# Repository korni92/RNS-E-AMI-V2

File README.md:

# RNS-E-AMI-V2
Replacement for AMI with more modern features

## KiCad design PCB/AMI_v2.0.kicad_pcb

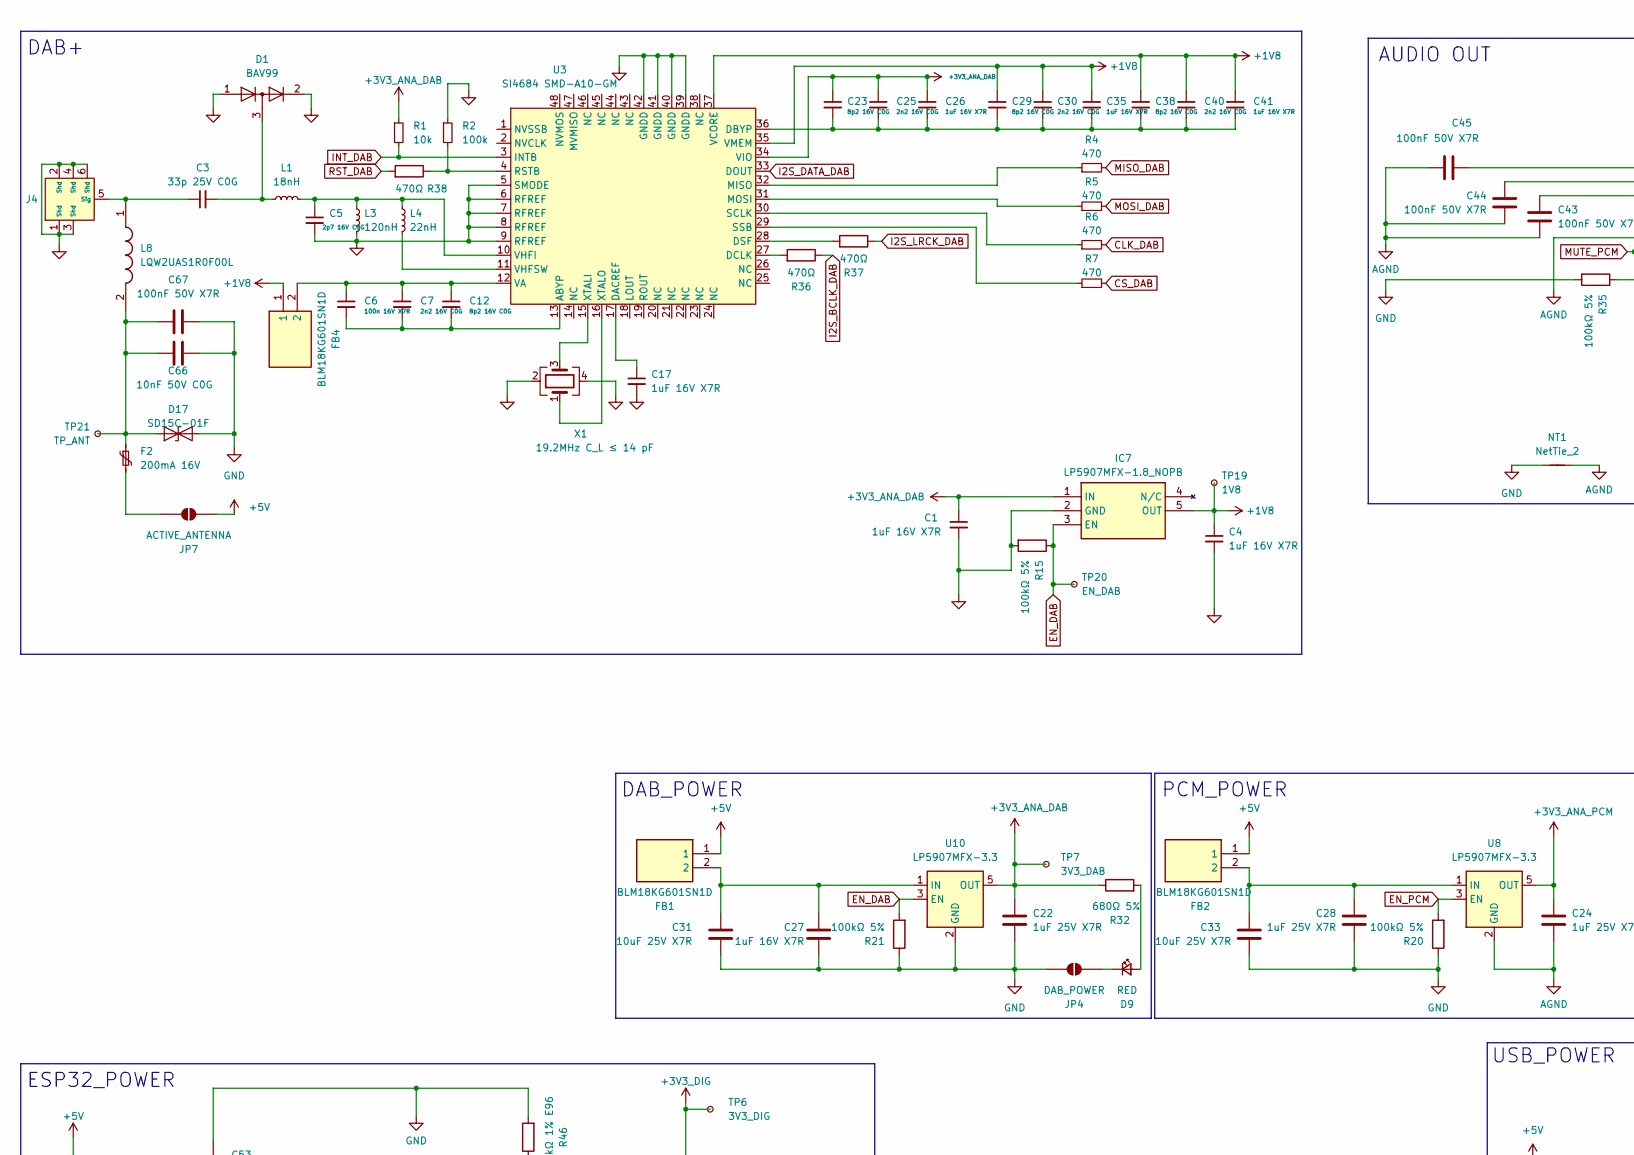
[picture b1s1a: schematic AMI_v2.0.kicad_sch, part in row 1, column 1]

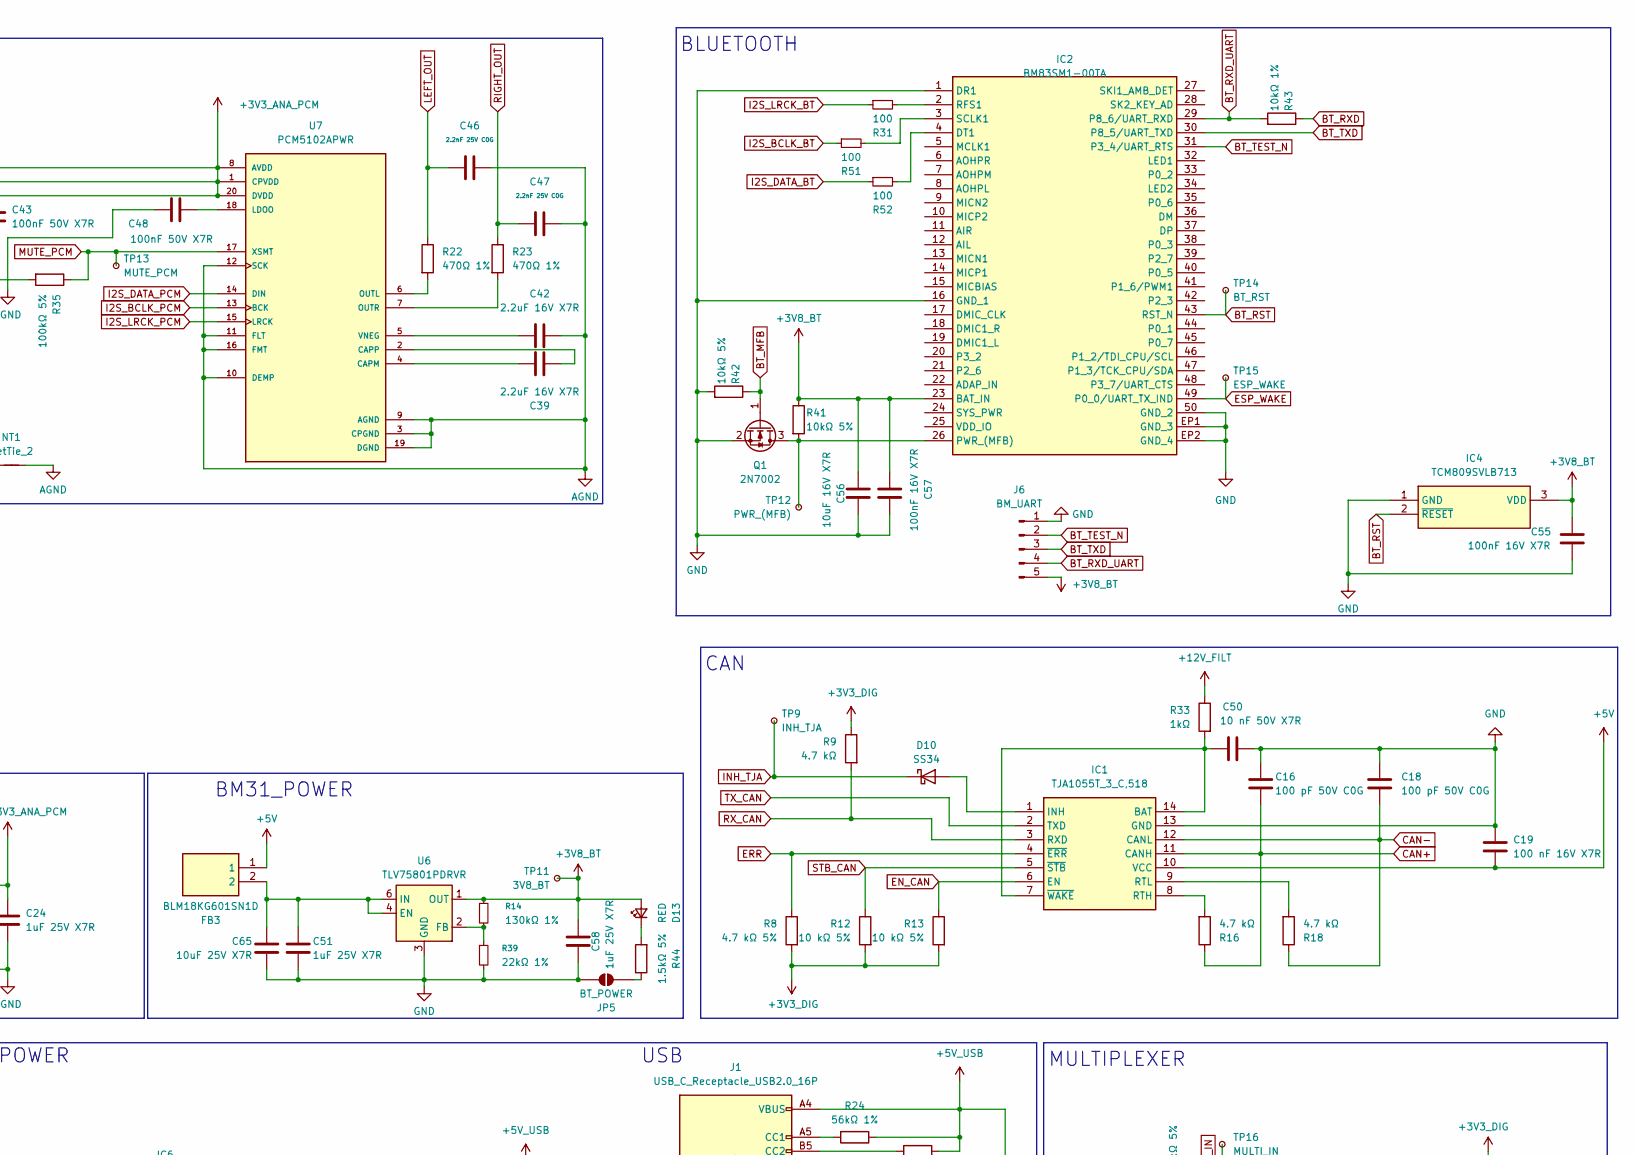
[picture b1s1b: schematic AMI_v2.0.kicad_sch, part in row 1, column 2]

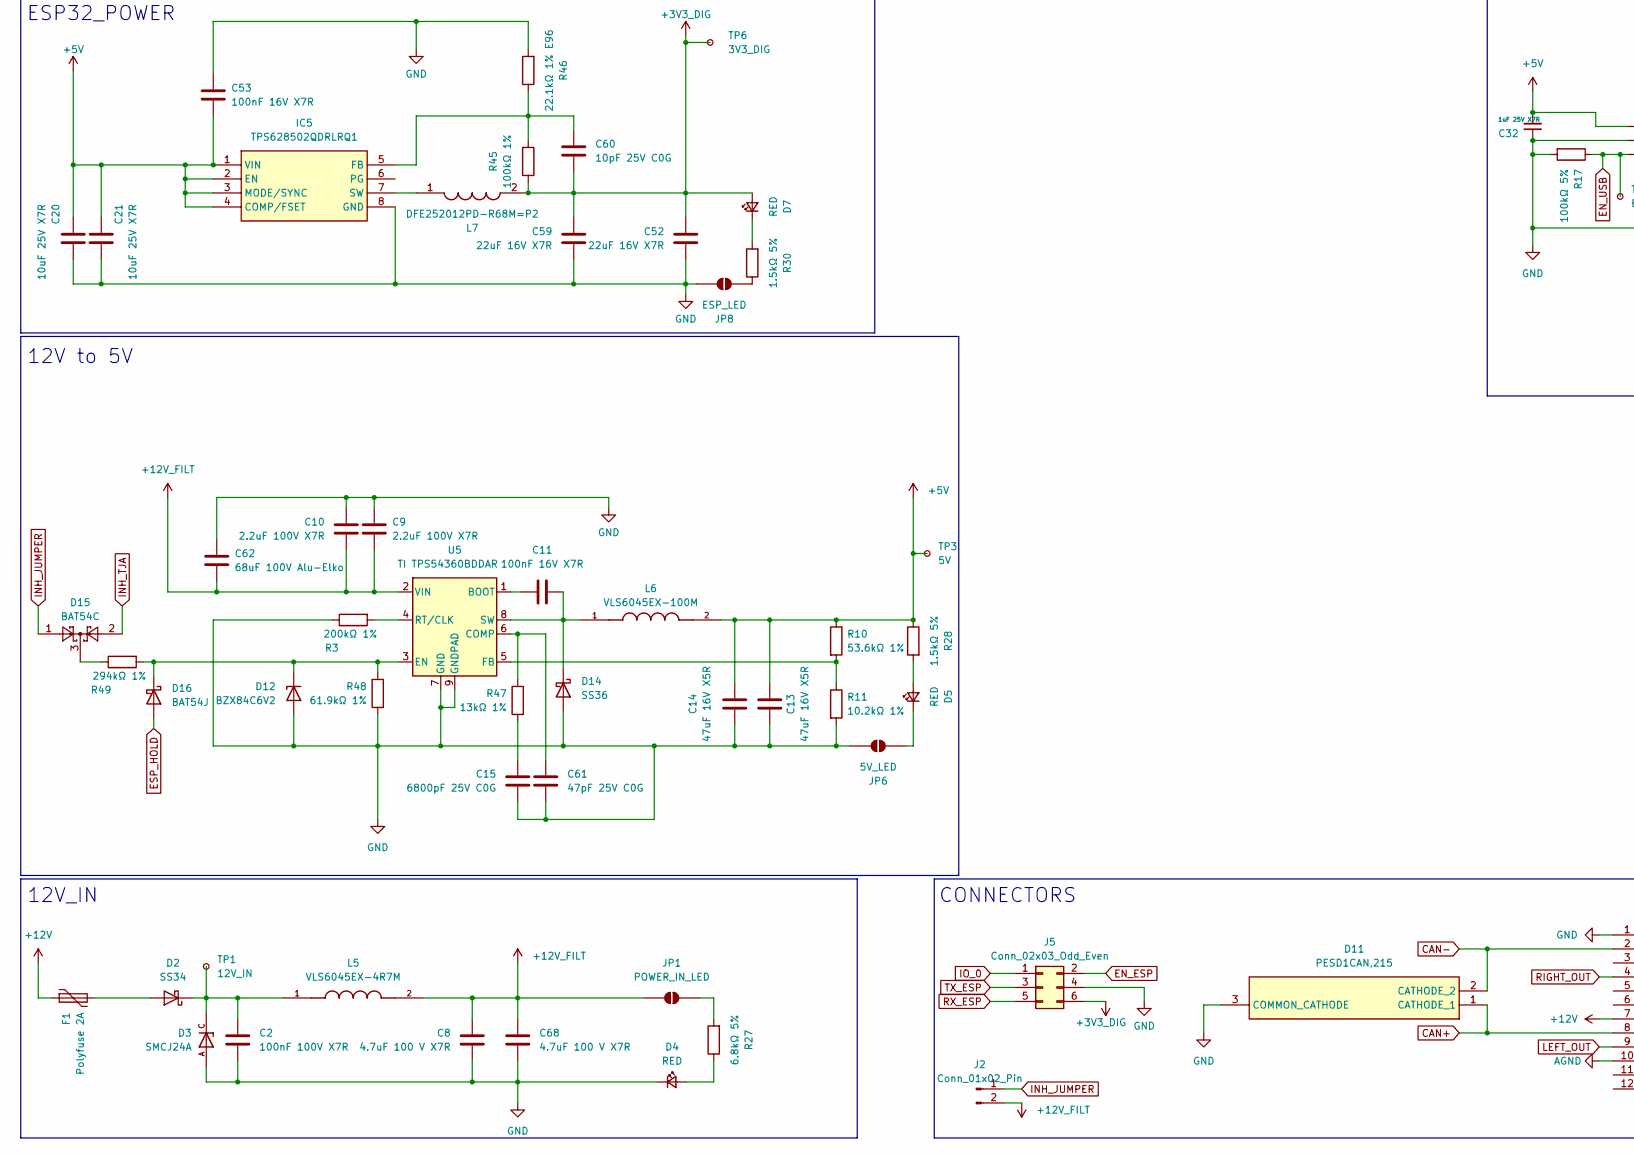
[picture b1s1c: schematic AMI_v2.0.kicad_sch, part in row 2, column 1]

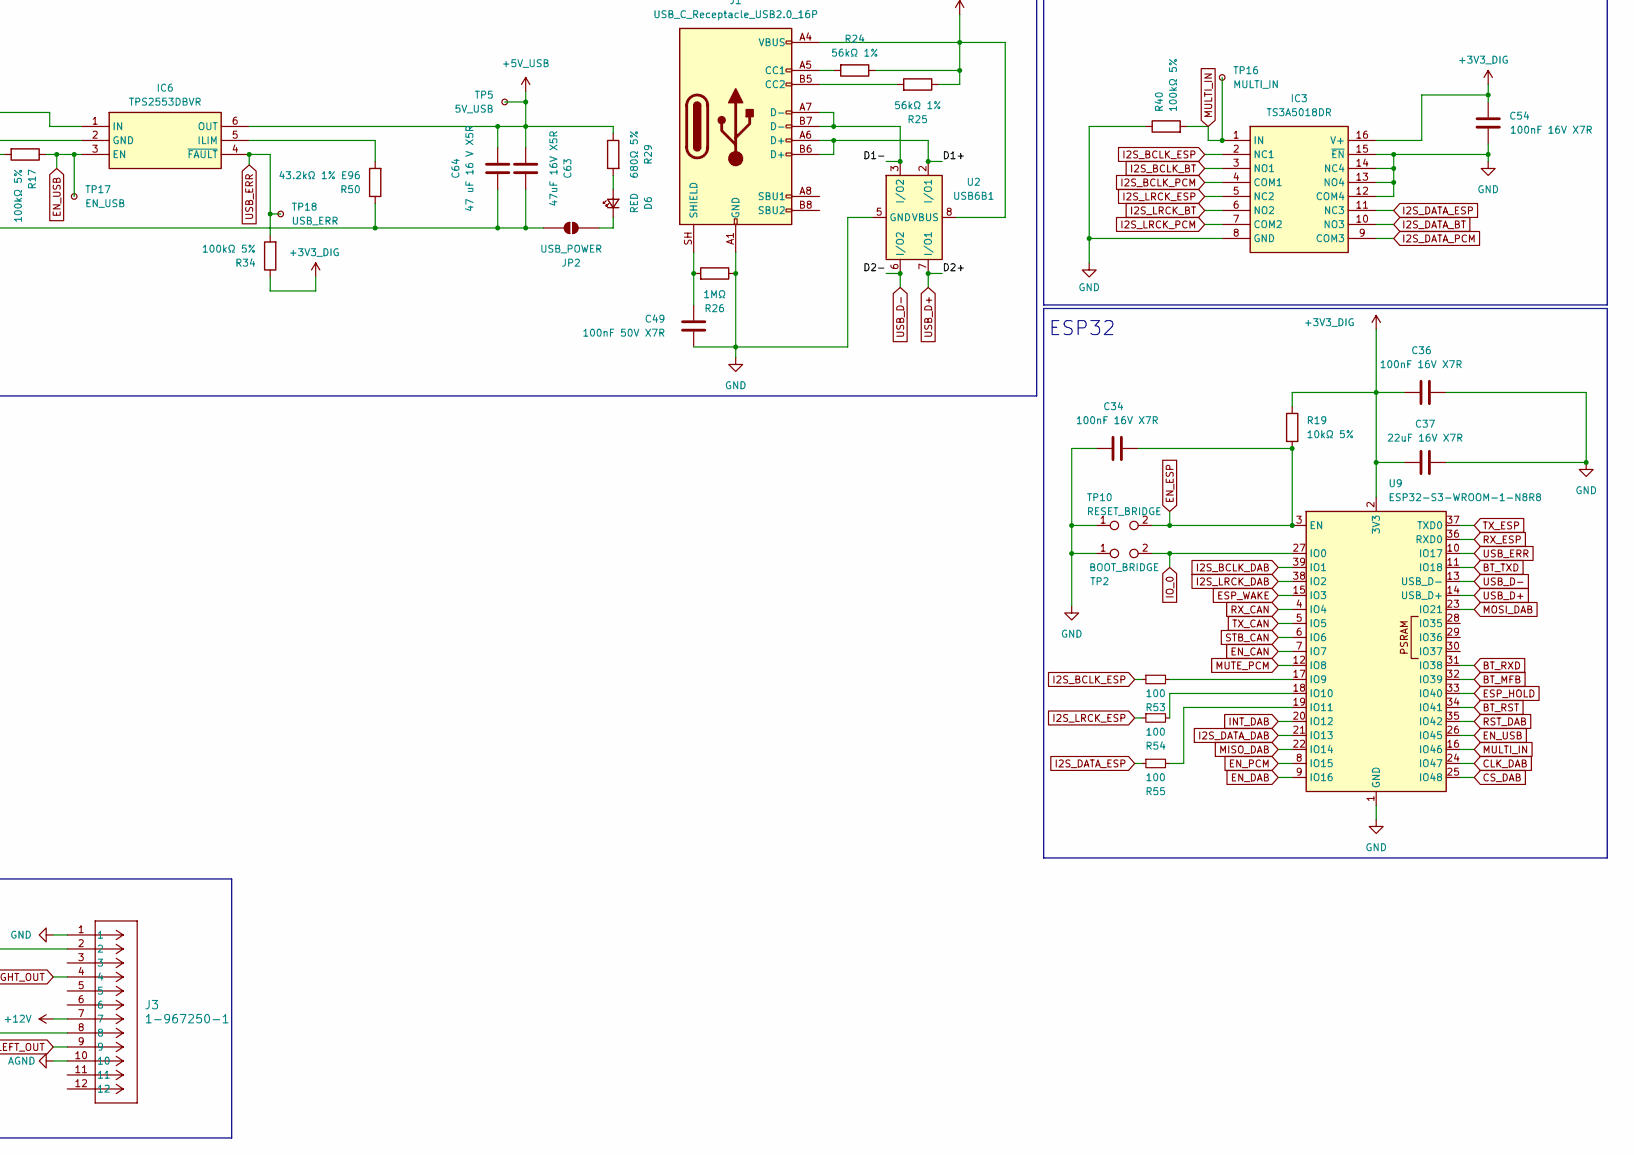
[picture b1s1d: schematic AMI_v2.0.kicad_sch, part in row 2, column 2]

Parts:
C1, C4, C17, C26, C27, C35, C41: 1uF 16V X7R; C_0603_1608Metric
C2: 100nF 100V X7R; C_0805_2012Metric
C3: 33p 25V C0G; C_0603_1608Metric
C5: 2p7 16V C0G; C_0603_1608Metric
C6: 100n 16V X7R; C_0603_1608Metric
C7, C25, C30, C40: 2n2 16V C0G; C_0603_1608Metric
C8, C68: 4.7uF 100 V X7R; C_1210_3225Metric
C9, C10: 2.2uF 100V X7R; C_1210_3225Metric
C11: 100nF 16V X7R; C_0603_1608Metric
C12, C23, C29, C38: 8p2 16V C0G; C_0603_1608Metric
C13, C14, C63: 47uF 16V X5R; C_1206_3216Metric
C15: 6800pF 25V C0G; C_0805_2012Metric
C16, C18: 100 pF 50V C0G; C_0603_1608Metric
C19: 100 nF 16V X7R; C_0603_1608Metric
C20, C21, C31, C33, C65: 10uF 25V X7R; C_0805_2012Metric
C22, C24, C28, C32, C51, C58: 1uF 25V X7R; C_0603_1608Metric
C34, C36, C53, C54, C55, C57: 100nF 16V X7R; C_0805_2012Metric
C37, C52, C59: 22uF 16V X7R; C_0805_2012Metric
C39, C42: 2.2uF 16V X7R; C_0603_1608Metric
C43, C44, C45, C48, C49, C67: 100nF 50V X7R; C_0805_2012Metric
C46, C47: 2.2nF 25V C0G; C_0603_1608Metric
C50: 10 nF 50V X7R; C_0603_1608Metric
C56: 10uF 16V X7R; C_1210_3225Metric
C60: 10pF 25V C0G; C_0603_1608Metric
C61: 47pF 25V C0G; C_0603_1608Metric
C62: 68uF 100V Alu-Elko; CP_Elec_10x10.5; Part JVJ100V68M10X10; LCSC C53120951
C64: 47 uF 16 V X5R; C_1206_3216Metric
C66: 10nF 50V C0G; C_0805_2012Metric
D1: BAV99; SOT-23
D2, D10: SS34; D_SMA
D3: SMCJ24A; DIOM6859X262N; PARTREV R2102
D4, D5, D6, D7, D9, D13: RED; LED_0603_1608Metric
D11: PESD1CAN,215; SOT95P230X110-3N; Mouser Part Number 771-PESD1CAN-T/R
D12: BZX84C6V2; SOT-23; LCSC C841160
D14: SS36; D_SMA
D15: BAT54C; SOT-23
D16: BAT54J; D_SOD-323F
D17: SD15C-01F; D_SOD-323; LCSC Part# C207245
F1: Polyfuse 2A; Fuse_1812_4532Metric
F2: 200mA 16V; Fuse_0603_1608Metric
FB1, FB2, FB3, FB4: BLM18KG601SN1D; BLM18SP221SN1B; Mouser Part Number 81-BLM18KG601SN1D
IC1: TJA1055T_3_C,518; SOIC127P600X175-14N; Mouser Part Number 771-TJA1055T3C518
IC2: BM83SM1-00TA; BM83SM100TA; Manufacturer_Part_Number BM83SM1-00TA; Mouser Part Number 579-BM83SM1-00TA
IC3: TS3A5018DR; SOIC127P600X175-16N; Mouser Part Number 595-TS3A5018DR
IC4: TCM809SVLB713; SOT65P210X110-3N; Mouser Part Number 579-TCM809SVLB713
IC5: TPS628502QDRLRQ1; SOTFL50P160X60-8N; Mouser Part Number 595-TPS628502QDRLRQ1
IC6: TPS2553DBVR; SOT95P280X145-6N; Mouser Part Number 595-TPS2553DBVR
IC7: LP5907MFX-1.8_NOPB; SOT95P280X145-5N; Mouser Part Number 595-LP5907MFX-1.8NPB
J1: USB_C_Receptacle_USB2.0_16P; USB_C_Receptacle_HCTL_HC-TYPE-C-16P-01A; LCSC Part# C2894897
J2: Conn_01x02_Pin; PinHeader_1x02_P2.54mm_Vertical
J3: 1-967250-1; CONN12_1-967250-1_TEC
J4: Fakra
J5: Conn_02x03_Odd_Even; PinHeader_2x03_P2.54mm_Vertical
J6: BM_UART; PinHeader_1x05_P2.54mm_Vertical
JP1: POWER_IN_LED; SolderJumper-2_P1.3mm_Open_RoundedPad1.0x1.5mm
JP2: USB_POWER; SolderJumper-2_P1.3mm_Open_RoundedPad1.0x1.5mm
JP4: DAB_POWER; SolderJumper-2_P1.3mm_Open_RoundedPad1.0x1.5mm
JP5: BT_POWER; SolderJumper-2_P1.3mm_Open_RoundedPad1.0x1.5mm
JP6: 5V_LED; SolderJumper-2_P1.3mm_Open_RoundedPad1.0x1.5mm
JP7: ACTIVE_ANTENNA; SolderJumper-2_P1.3mm_Open_RoundedPad1.0x1.5mm
JP8: ESP_LED; SolderJumper-2_P1.3mm_Open_RoundedPad1.0x1.5mm
L1: 18nH; L_0603_1608Metric; LCSC Part# C86133
L3: 120nH; L_0603_1608Metric; LCSC Part# C86138
L4: 22nH; L_0603_1608Metric; LCSC Part# C84341
L5: VLS6045EX-4R7M; IND_VLS6045EX-4R7M; PARTREV N/A; LCSC Part# C307880
L6: VLS6045EX-100M; IND_VLS6045EX-100M; PARTREV N/A; LCSC Part# C360734
L7: DFE252012PD-R68M=P2; DFE2HCAH1R0MJ0L; Mouser Part Number 81-DFE252012PDR68MP2
L8: LQW2UAS1R0F00L; LQW2UAS12NG00L; Mouser Part Number 81-LQW2UAS1R0F00L
NT1: NetTie_2; NetTie-2_SMD_Pad0.5mm
Q1: 2N7002; SOT-23; LCSC Part# C65189
R1: 10k; R_0603_1608Metric
R2: 100k; R_0603_1608Metric
R3: 200kΩ 1%; R_0603_1608Metric
R4, R5, R6, R7: 470; R_0603_1608Metric
R8: 4.7 kΩ 5%; R_0603_1608Metric
R9: 4.7 kΩ; R_0603_1608Metric
R10: 53.6kΩ 1%; R_0603_1608Metric
R11: 10.2kΩ 1%; R_0603_1608Metric
R12, R13: 10 kΩ 5%; R_0603_1608Metric
R14: 130kΩ 1%; R_0603_1608Metric
R15, R17, R20, R21, R34, R35, R40: 100kΩ 5%; R_0603_1608Metric
R16, R18: 4.7 kΩ; R_0805_2012Metric
R19, R41, R42: 10kΩ 5%; R_0603_1608Metric
R22, R23: 470Ω 1%; R_0603_1608Metric
R24, R25: 56kΩ 1%; R_0603_1608Metric
R26: 1MΩ; R_0603_1608Metric
R27: 6.8kΩ 5%; R_0603_1608Metric
R28, R30, R44: 1.5kΩ 5%; R_0603_1608Metric
R29, R32: 680Ω 5%; R_0603_1608Metric
R31, R51, R52, R53, R54, R55: 100; R_0603_1608Metric
R33: 1kΩ; R_0603_1608Metric
R36, R37, R38: 470Ω; R_0603_1608Metric
R39: 22kΩ 1%; R_0603_1608Metric
R43: 10kΩ 1%; R_0603_1608Metric
R45: 100kΩ 1%; R_0603_1608Metric
R46: 22.1kΩ 1% E96; R_0603_1608Metric
R47: 13kΩ 1%; R_0603_1608Metric
R48: 61.9kΩ 1%; R_0603_1608Metric
R49: 294kΩ 1%; R_0603_1608Metric
R50: 43.2kΩ 1% E96; R_0603_1608Metric
TP1: 12V_IN; TestPoint_Pad_D1.5mm
TP2: BOOT_BRIDGE; SolderJumper-2_P1.3mm_Open_Pad1.0x1.5mm
TP3: 5V; TestPoint_Pad_D1.5mm
TP5: 5V_USB; TestPoint_Pad_D1.5mm
TP6: 3V3_DIG; TestPoint_Pad_D1.5mm
TP7: 3V3_DAB; TestPoint_Pad_D1.5mm
TP9: INH_TJA; TestPoint_Pad_D1.5mm
TP10: RESET_BRIDGE; SolderJumper-2_P1.3mm_Open_Pad1.0x1.5mm
TP11: 3V8_BT; TestPoint_Pad_D1.5mm
TP12: PWR_(MFB); TestPoint_Pad_D1.5mm
TP13: MUTE_PCM; TestPoint_Pad_D1.5mm
TP14: BT_RST; TestPoint_Pad_D1.5mm
TP15: ESP_WAKE; TestPoint_Pad_D1.5mm
TP16: MULTI_IN; TestPoint_Pad_D1.5mm
TP17: EN_USB; TestPoint_Pad_D1.5mm
TP18: USB_ERR; TestPoint_Pad_D1.5mm
TP19: 1V8; TestPoint_Pad_D1.5mm
TP20: EN_DAB; TestPoint_Pad_D1.5mm
TP21: TP_ANT; TestPoint_Pad_D1.5mm
U2: USB6B1; SOIC-8_3.9x4.9mm_P1.27mm; LCSC Part# C283483
U3: SI4684 SMD-A10-GM; QFN-48-1EP_7x7mm_P0.5mm_EP5.3x5.3mm; LCSC Part# C1526088
U5: TI TPS54360BDDAR; TI_SO-PowerPAD-8_ThermalVias; LCSC Part# C524806
U6: TLV75801PDRVR; WSON-6-1EP_2x2mm_P0.65mm_EP1x1.6mm; LCSC Part# C2876308
U7: PCM5102APWR; SOP65P640X120-20N; PARTREV C; LCSC Part# C1520792
U8, U10: LP5907MFX-3.3; SOT-23-5; LCSC Part# C80670
U9: ESP32-S3-WROOM-1-N8R8; ESP32-S3-WROOM-1; LCSC Part# C2913201
X1: 19.2MHz C_L ≤ 14 pF; Crystal_SMD_3225-4Pin_3.2x2.5mm

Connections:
+1V8: C4.1, C29.1, C30.1, C35.1, C38.1, C40.1, C41.1, FB4.1, IC7.5 (OUT), TP19.1 (1_1), U3.35 (VMEM), U3.37 (VCORE)
+3V3_ANA_DAB: C1.1, C22.1, C23.1, C25.1, C26.1, IC7.1 (IN), R1.1, R32.1, TP7.1 (1_1), U3.34 (VIO), U10.5 (OUT)
+3V3_ANA_PCM: C24.1, C43.2, C44.2, C45.2, U7.1 (CPVDD), U7.8 (AVDD), U7.20 (DVDD), U8.5 (OUT)
+3V3_DIG: C36.1, C37.2, C52.2, C54.1, C59.2, C60.1, D7.2 (A), IC3.16 (V+), J5.6, L7.2, R8.2, R9.1, R12.2, R13.2, R19.1, R34.1, R45.1, TP6.1 (1_1), U9.2 (3V3)
+3V8_BT: C55.1, C56.2, C57.2, C58.2, D13.2 (A), IC2.23 (BAT_IN), IC4.3 (VDD), J6.5, R14.1, R41.1, TP11.1 (1_1), U6.1 (OUT)
+5V: C13.2, C14.1, C19.2, C20.1, C21.1, C32.2, C53.2, FB1.1, FB2.1, FB3.1, IC1.10 (VCC), IC5.1 (VIN), IC5.2 (EN), IC5.3 (MODE/SYNC), IC5.4 (COMP/FSET), IC6.1 (IN), JP7.2 (B), L6.2, R10.1, R28.1, TP3.1 (1_1)
+5V_USB: C63.2, C64.1, IC6.6 (OUT), J1.A4 (VBUS), J1.A9 (VBUS), J1.B4 (VBUS), J1.B9 (VBUS), R24.1, R25.1, R29.1, TP5.1 (1_1), U2.1 (VBUS), U2.8 (VBUS)
+12V: F1.1, J3.7
+12V_FILT: C8.1, C9.2, C10.2, C62.2, C68.1, J2.2, JP1.1 (A), L5.2, R33.1, U5.2 (VIN)
/D1+: J1.A6 (D+), J1.B6 (D+), U2.2 (I/O1)
/D1-: J1.A7 (D-), J1.B7 (D-), U2.3 (I/O2)
AGND: C24.2, C42.1, C43.1, C44.1, C45.1, C46.1, C47.1, C48.1, J3.10, NT1.2, U7.3 (CPGND), U7.9 (AGND), U7.10 (DEMP), U7.11 (FLT), U7.12 (SCK), U7.16 (FMT), U7.19 (DGND), U8.2 (GND)
BT_MFB: Q1.1 (G), R42.1, U9.32 (IO39)
BT_RST: IC2.43 (RST_N), IC4.2 (~RESET), TP14.1 (1_1), U9.34 (IO41)
BT_RXD: R43.1, U9.31 (IO38)
BT_RXD_UART: IC2.29 (P8_6/UART_RXD), J6.4, R43.2
BT_TEST_N: IC2.31 (P3_4/UART_RTS), J6.2
BT_TXD: IC2.30 (P8_5/UART_TXD), J6.3, U9.11 (IO18)
CAN+: C16.2, D11.1 (CATHODE_1), IC1.11 (CANH), J3.8, R16.1
CAN-: C18.2, D11.2 (CATHODE_2), IC1.12 (CANL), J3.2, R18.1
CLK_DAB: R6.2, U9.24 (IO47)
CS_DAB: R7.2, U9.25 (IO48)
EN_CAN: IC1.6 (EN), R13.1, U9.7 (IO7)
EN_DAB: IC7.3 (EN), R15.1, R21.2, TP20.1 (1_1), U9.9 (IO16), U10.3 (EN)
EN_ESP: C34.2, J5.2, R19.2, TP10.2, U9.3 (EN)
EN_PCM: R20.2, U8.3 (EN), U9.8 (IO15)
EN_USB: IC6.3 (EN), R17.1, TP17.1 (1_1), U9.26 (IO45)
ERR: IC1.4 (~ERR), R8.1
ESP_HOLD: D16.2 (A), U9.33 (IO40)
ESP_WAKE: IC2.49 (P0_0/UART_TX_IND), TP15.1 (1_1), U9.15 (IO3)
GND: C1.2, C2.2, C4.2, C5.2, C8.2, C9.1, C10.1, C13.1, C14.2, C15.2, C16.1, C17.2, C18.1, C19.1, C20.2, C21.2, C22.2, C27.2, C28.2, C31.2, C32.1, C33.2, C34.1, C36.2, C37.1, C49.1, C50.1, C51.2, C52.1, C53.1, C54.2, C55.2, C56.1, C57.1, C58.1, C59.1, C61.2, C62.1, C63.1, C64.2, C65.2, C66.1, C67.1, C68.2, D1.1 (K), D1.2 (A), D3.A, D4.1 (K), D11.3 (COMMON_CATHODE), D12.1 (A), D14.2 (A), D17.2 (A2), IC1.13 (GND), IC2.1 (DR1), IC2.16 (GND_1), IC2.50 (GND_2), IC2.EP1 (GND_3), IC2.EP2 (GND_4), IC3.8 (GND), IC3.12 (COM4), IC3.13 (NO4), IC3.14 (NC4), IC3.15 (~EN), IC4.1 (GND), IC5.8 (GND), IC6.2 (GND), IC7.2 (GND), J1.A1 (GND), J1.A12 (GND), J1.B1 (GND), J1.B12 (GND), J3.1, J4.1 (Shd), J4.2 (Shd), J4.3 (Shd), J4.4 (Shd), J4.6 (Shd), J5.4, J6.1, JP2.1 (A), JP4.1 (A), JP5.1 (A), JP6.1 (A), JP8.1 (A), L3.2, NT1.1, Q1.2 (S), R2.1, R3.1, R11.2, R15.2, R17.2, R20.1, R21.1, R26.1, R35.2, R39.2, R40.1, R42.2, R46.2, R48.2, R50.1, TP2.1, TP10.1, U2.4 (GND), U2.5 (GND), U3.5 (SMODE), U3.6 (RFREF), U3.7 (RFREF), U3.8 (RFREF), U3.9 (RFREF), U3.39 (GNDD), U3.40 (GNDD), U3.41 (GNDD), U3.42 (GNDD), U3.49 (GND), U5.7 (GND), U5.9 (GNDPAD), U6.3 (GND), U6.7 (GND), U9.1 (GND), U9.40 (GND), U9.41 (GND), U10.2 (GND), X1.2, X1.4
I2S_BCLK_BT: IC3.3 (NO1), R51.1
I2S_BCLK_DAB: R36.1, U9.39 (IO1)
I2S_BCLK_ESP: IC3.2 (NC1), R53.1
I2S_BCLK_PCM: IC3.4 (COM1), U7.13 (BCK)
I2S_DATA_BT: IC3.10 (NO3), R52.1
I2S_DATA_DAB: U3.33 (DOUT), U9.21 (IO13)
I2S_DATA_ESP: IC3.11 (NC3), R55.1
I2S_DATA_PCM: IC3.9 (COM3), U7.14 (DIN)
I2S_LRCK_BT: IC3.6 (NO2), R31.1
I2S_LRCK_DAB: R37.1, U9.38 (IO2)
I2S_LRCK_ESP: IC3.5 (NC2), R54.1
I2S_LRCK_PCM: IC3.7 (COM2), U7.15 (LRCK)
INH_JUMPER: D15.1, J2.1
INH_TJA: D10.1 (K), D15.2, TP9.1 (1_1)
INT_DAB: R1.2, U3.3 (INTB), U9.20 (IO12)
IO_0: J5.1, TP2.2, U9.27 (IO0)
LEFT_OUT: C46.2, J3.9, R22.1
MISO_DAB: R4.2, U9.22 (IO14)
MOSI_DAB: R5.2, U9.23 (IO21)
MULTI_IN: IC3.1 (IN), R40.2, TP16.1 (1_1), U9.16 (IO46)
MUTE_PCM: R35.1, TP13.1 (1_1), U7.17 (XSMT), U9.12 (IO8)
unnamed: C3.2, D1.3 (K), L1.1
unnamed: C15.1, R47.2
unnamed: D2.2 (A), F1.2
unnamed: C2.1, D2.1 (K), D3.C, L5.1, TP1.1 (1_1)
unnamed: D4.2 (A), R27.1
unnamed: D5.2 (A), R28.2
unnamed: D5.1 (K), JP6.2 (B)
unnamed: D6.2 (A), R29.2
unnamed: D6.1 (K), JP2.2 (B)
unnamed: D7.1 (K), R30.2
unnamed: D9.2 (A), R32.2
unnamed: D9.1 (K), JP4.2 (B)
unnamed: D10.2 (A), IC1.1 (INH)
unnamed: D12.3 (K), D16.1 (K), R48.1, R49.2, U5.3 (EN)
unnamed: D13.1 (K), R44.2
unnamed: C11.1, D14.1 (K), L6.1, U5.8 (SW)
unnamed: D15.3, R49.1
unnamed: C66.2, C67.2, D17.1 (A1), F2.1, L8.2, TP21.1 (1_1)
unnamed: C50.2, IC1.7 (~WAKE), IC1.14 (BAT), R33.2
unnamed: IC1.8 (RTH), R16.2
unnamed: IC1.9 (RTL), R18.2
unnamed: IC2.4 (DT1), R52.2
unnamed: IC2.26 (PWR_(MFB)), Q1.3 (D), R41.2, TP12.1 (1_1)
unnamed: IC2.2 (RFS1), R31.2
unnamed: IC2.3 (SCLK1), R51.2
unnamed: C60.2, IC5.5 (FB), R45.2, R46.1
unnamed: IC5.7 (SW), L7.1
unnamed: IC6.5 (ILIM), R50.2
unnamed: J1.A5 (CC1), R24.2
unnamed: J1.B5 (CC2), R25.2
unnamed: C49.2, J1.SH (SHIELD), R26.2
unnamed: C3.1, J4.5 (Sig), L8.1
unnamed: JP1.2 (B), R27.2
unnamed: JP5.2 (B), R44.1
unnamed: F2.2, JP7.1 (A)
unnamed: JP8.2 (B), R30.1
unnamed: C6.2, C7.2, C12.2, U3.13 (ABYP)
unnamed: C17.1, U3.17 (DACREF)
unnamed: C23.2, C25.2, C26.2, C29.2, C30.2, C35.2, C38.2, C40.2, C41.2, U3.36 (DBYP)
unnamed: R36.2, U3.27 (DCLK)
unnamed: R37.2, U3.28 (DSF)
unnamed: R4.1, U3.32 (MISO)
unnamed: R5.1, U3.31 (MOSI)
unnamed: R2.2, R38.1, U3.4 (RSTB)
unnamed: R6.1, U3.30 (SCLK)
unnamed: R7.1, U3.29 (SSB)
unnamed: C6.1, C7.1, C12.1, FB4.2, U3.12 (VA)
unnamed: C5.1, L1.2, L3.1, L4.1, U3.10 (VHFI)
unnamed: L4.2, U3.11 (VHFSW)
unnamed: U3.15 (XTALI), X1.3
unnamed: U3.16 (XTALO), X1.1
unnamed: C11.2, U5.1 (BOOT)
unnamed: C61.1, R47.1, U5.6 (COMP)
unnamed: R10.2, R11.1, U5.5 (FB)
unnamed: R3.2, U5.4 (RT/CLK)
unnamed: C51.1, C65.1, FB3.2, U6.4 (EN), U6.6 (IN)
unnamed: R14.2, R39.1, U6.2 (FB)
unnamed: C39.2, U7.4 (CAPM)
unnamed: C39.1, U7.2 (CAPP)
unnamed: C48.2, U7.18 (LDOO)
unnamed: R22.2, U7.6 (OUTL)
unnamed: R23.2, U7.7 (OUTR)
unnamed: C42.2, U7.5 (VNEG)
unnamed: C28.1, C33.1, FB2.2, U8.1 (IN)
unnamed: R53.2, U9.17 (IO9)
unnamed: R54.2, U9.18 (IO10)
unnamed: R55.2, U9.19 (IO11)
unnamed: C27.1, C31.1, FB1.2, U10.1 (IN)
RIGHT_OUT: C47.2, J3.4, R23.1
RST_DAB: R38.2, U9.35 (IO42)
RX_CAN: IC1.3 (RXD), R9.2, U9.4 (IO4)
RX_ESP: J5.5, U9.36 (RXD0)
STB_CAN: IC1.5 (~STB), R12.1, U9.6 (IO6)
TX_CAN: IC1.2 (TXD), U9.5 (IO5)
TX_ESP: J5.3, U9.37 (TXD0)
USB_D+: U2.7 (I/O1), U9.14 (USB_D+)
USB_D-: U2.6 (I/O2), U9.13 (USB_D-)
USB_ERR: IC6.4 (~FAULT), R34.2, TP18.1 (1_1), U9.10 (IO17)

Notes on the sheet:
CAN
BLUETOOTH
USB
ESP32
12V to 5V
DAB_POWER
12V_IN
AUDIO OUT
CONNECTORS
PCM_POWER
BM31_POWER
DAB+
MULTIPLEXER
USB_POWER
ESP32_POWER

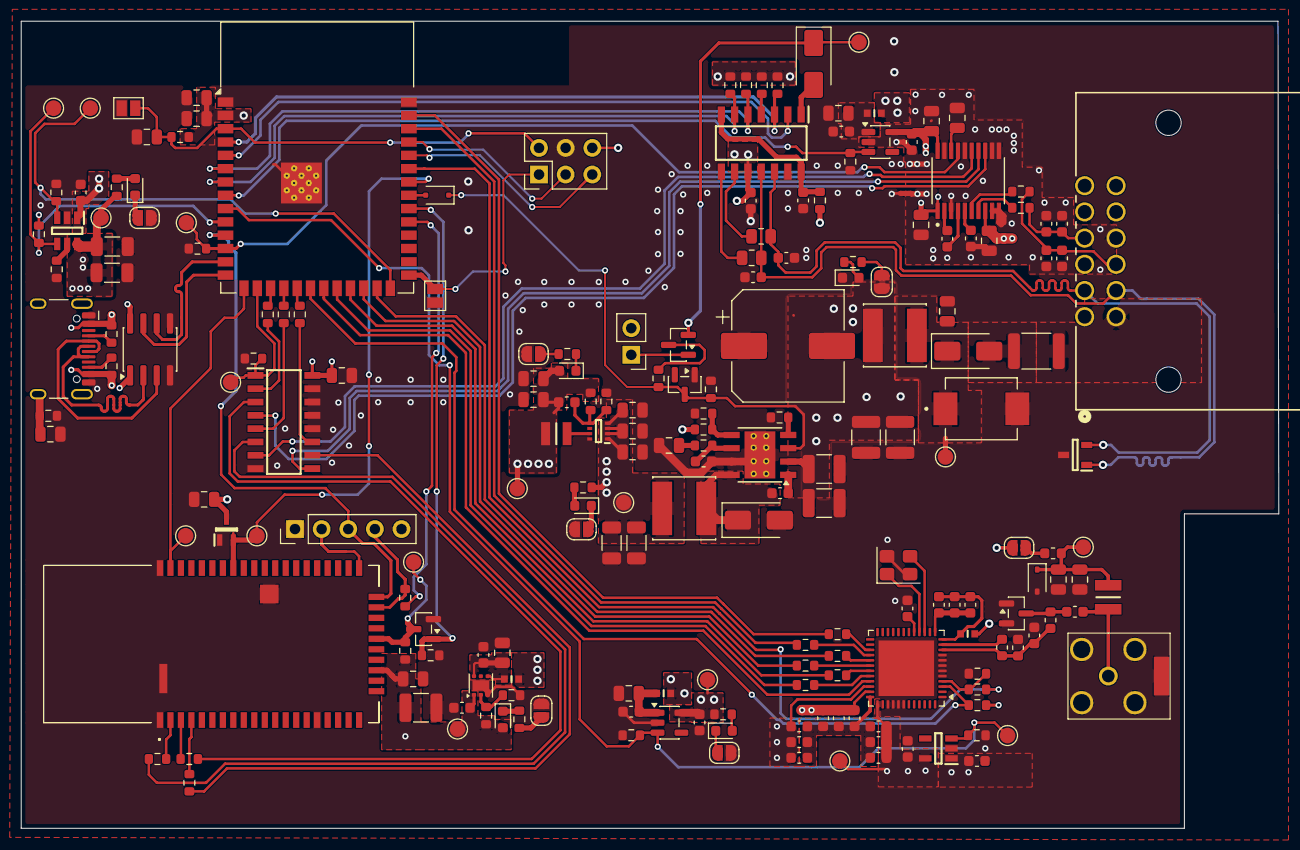
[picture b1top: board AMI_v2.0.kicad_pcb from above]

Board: 4 copper layers, 120.0 x 77.0 mm, 202 parts (0 on the bottom side), 130 nets.
